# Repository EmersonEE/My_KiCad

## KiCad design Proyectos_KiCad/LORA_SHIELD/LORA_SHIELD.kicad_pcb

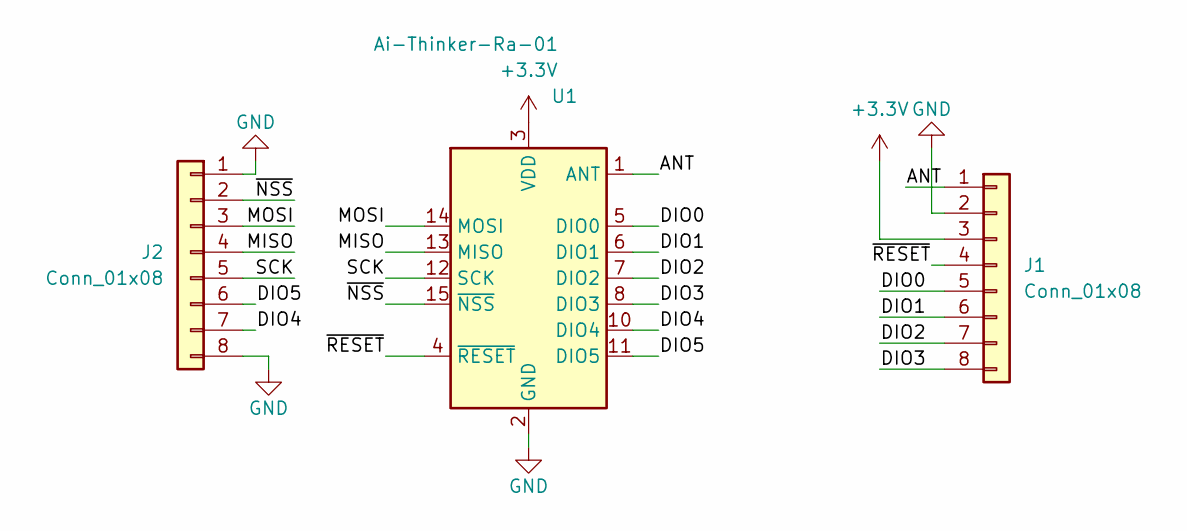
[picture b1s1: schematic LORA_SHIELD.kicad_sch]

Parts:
J1, J2: Conn_01x08; PinHeader_1x08_P2.54mm_Vertical
U1: Ai-Thinker-Ra-01; Ai-Thinker-Ra-01-LoRa

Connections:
+3.3V: J1.3, U1.3 (VDD)
/ANT: J1.1, U1.1 (ANT)
/DIO0: J1.5, U1.5 (DIO0)
/DIO1: J1.6, U1.6 (DIO1)
/DIO2: J1.7, U1.7 (DIO2)
/DIO3: J1.8, U1.8 (DIO3)
/DIO4: J2.7, U1.10 (DIO4)
/DIO5: J2.6, U1.11 (DIO5)
/MISO: J2.4, U1.13 (MISO)
/MOSI: J2.3, U1.14 (MOSI)
/SCK: J2.5, U1.12 (SCK)
/~NSS: J2.2, U1.15 (~NSS)
/~RESET: J1.4, U1.4 (~RESET)
GND: J1.2, J2.1, J2.8, U1.2 (GND), U1.9 (GND), U1.16 (GND)

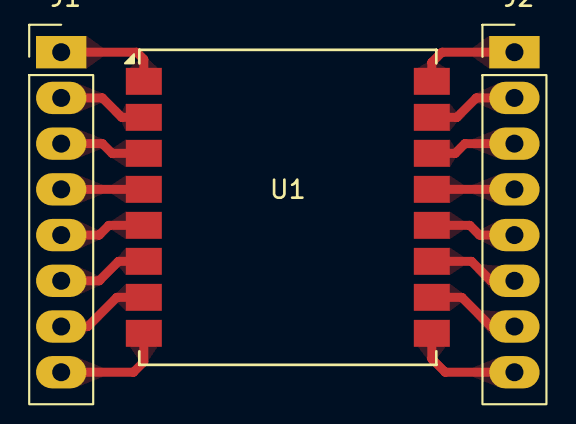
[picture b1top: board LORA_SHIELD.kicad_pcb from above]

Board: 2 copper layers, 3 parts (0 on the bottom side), 14 nets.

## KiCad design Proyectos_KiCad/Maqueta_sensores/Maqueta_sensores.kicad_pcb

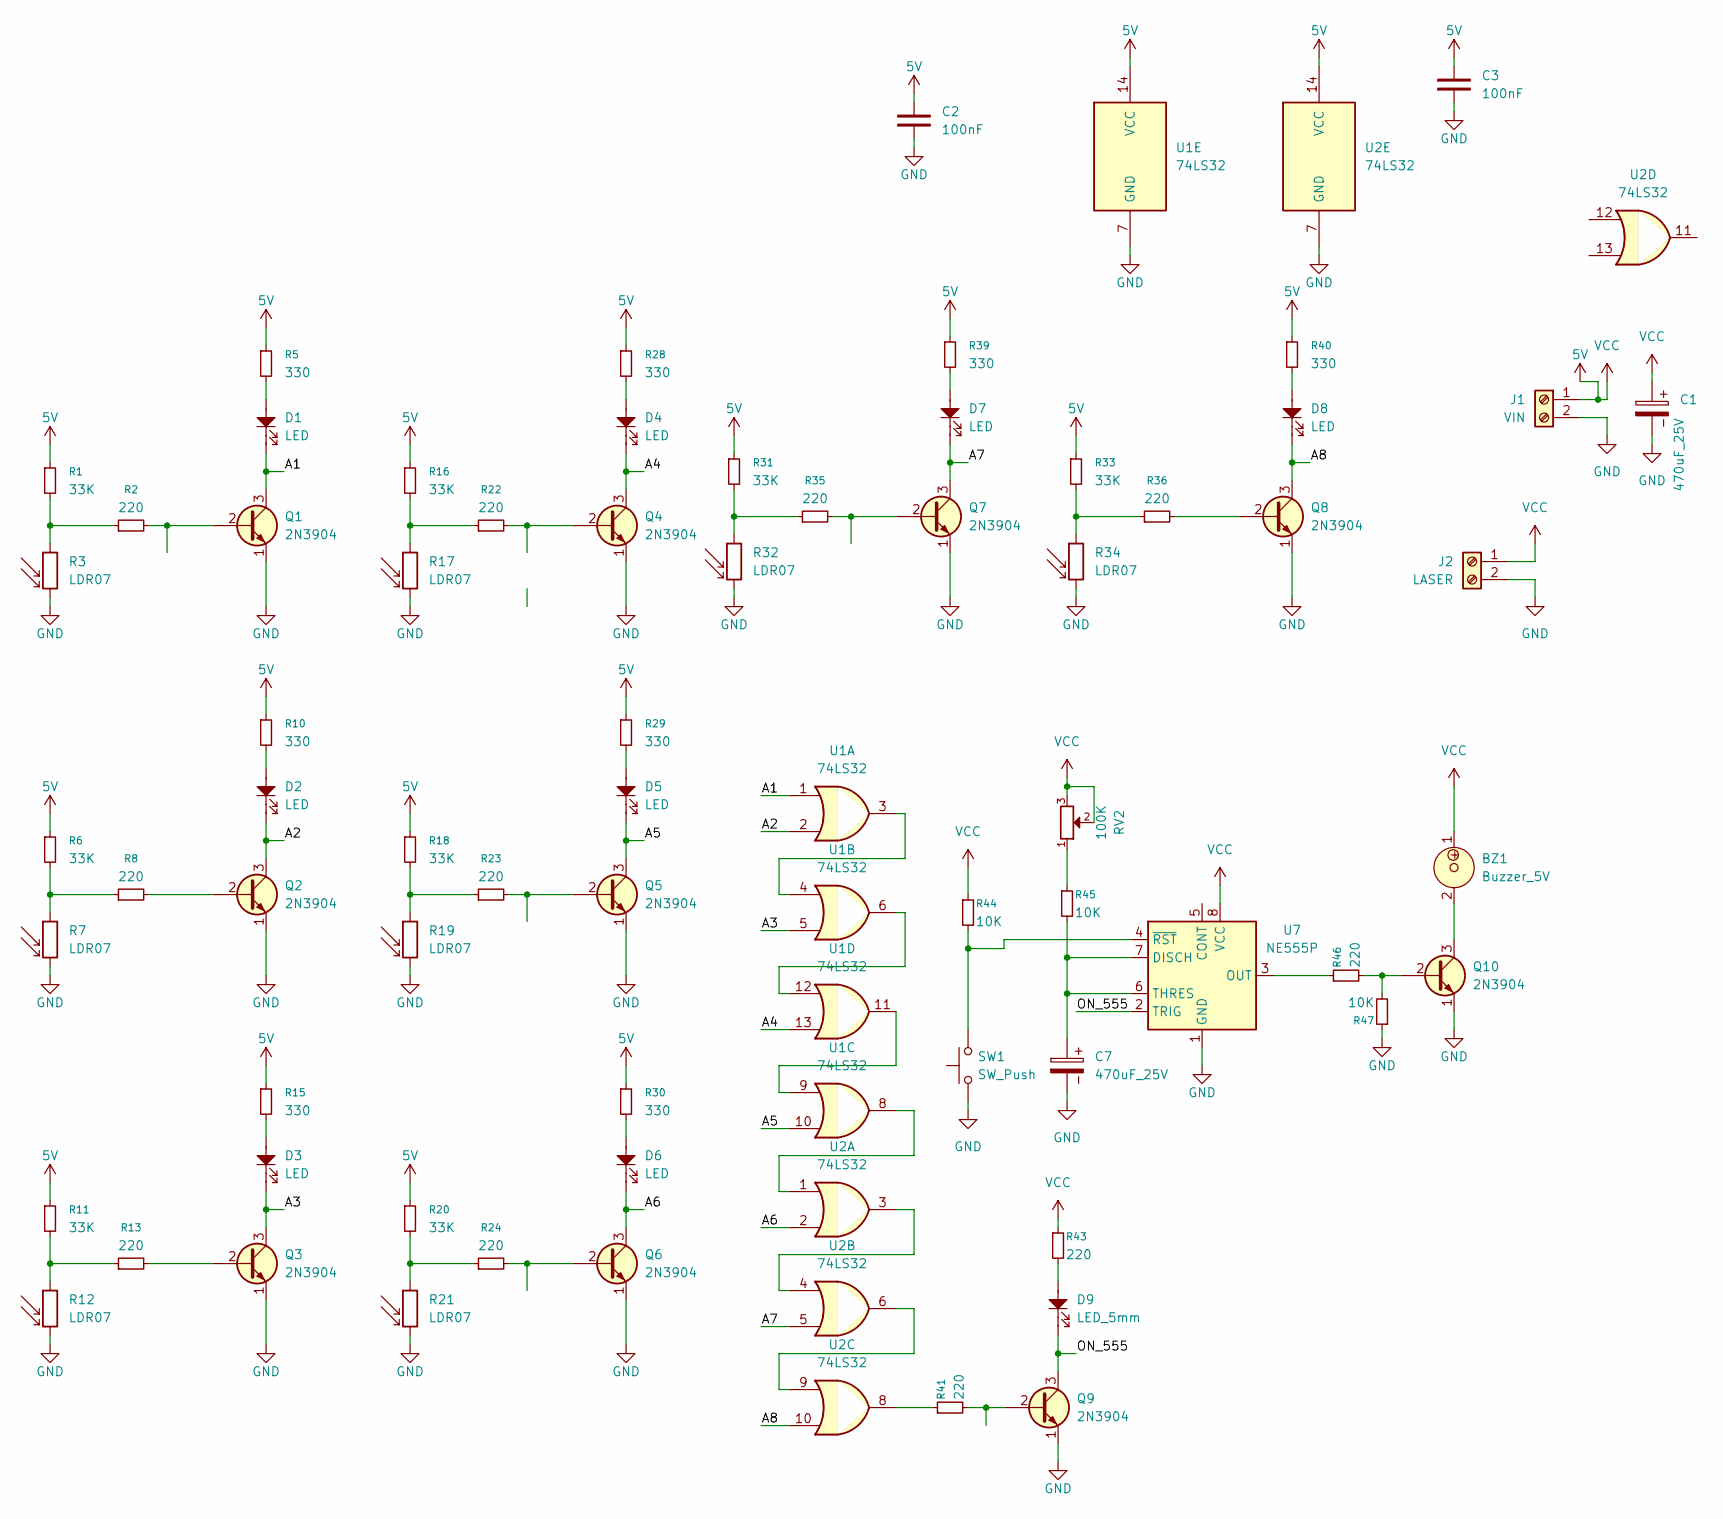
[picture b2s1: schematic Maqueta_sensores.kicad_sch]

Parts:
BZ1: Buzzer_5V; MagneticBuzzer_ProSignal_ABT-410-RC
C1, C7: 470uF_25V; CP_Radial_D8.0mm_P3.50mm
C2, C3: 100nF; C_Disc_D5.0mm_W2.5mm_P2.50mm
D1, D2, D3, D4, D5, D6, D7, D8: LED; LED_D5.0mm
D9: LED_5mm; LED_D5.0mm_Clear
J1: VIN; TerminalBlock_Phoenix_MKDS-1,5-2-5.08_1x02_P5.08mm_Horizont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
J2: LASER; TerminalBlock_Phoenix_MKDS-1,5-2-5.08_1x02_P5.08mm_Horizont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
Q1, Q2, Q3, Q4, Q5, Q6, Q7, Q8, Q9, Q10: 2N3904; TO-92_Inline_Wide_EBC
R1, R6, R11, R16, R18, R20, R31, R33: 33K; R_Axial_DIN0207_L6.3mm_D2.5mm_P10.16mm_Horizontal
R2, R8, R13, R22, R23, R24, R35, R36, R41, R43, R46: 220; R_Axial_DIN0207_L6.3mm_D2.5mm_P10.16mm_Horizontal
R3, R7, R12, R17, R19, R21, R32, R34: LDR07; R_LDR_5.1x4.3mm_P3.4mm_Vertical
R5, R10, R15, R28, R29, R30, R39, R40: 330; R_Axial_DIN0207_L6.3mm_D2.5mm_P10.16mm_Horizontal
R44, R45, R47: 10K; R_Axial_DIN0207_L6.3mm_D2.5mm_P10.16mm_Horizontal
RV2: 100K; Potentiometer_Alps_RK163_Single_Horizontal
SW1: SW_Push; SW_PUSH_6mm
U1, U2: 74LS32; DIP-14_W7.62mm_LongPads
U7: NE555P; DIP-8_W7.62mm_LongPads

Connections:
5V: BZ1.1, C1.1, C2.2, C3.2, J1.1, J2.1, R1.1, R5.1, R6.1, R10.1, R11.1, R15.1, R16.1, R18.1, R20.1, R28.1, R29.1, R30.1, R31.1, R33.1, R39.1, R40.1, R43.1, R44.1, RV2.2, RV2.3, U1.14 (VCC), U2.14 (VCC), U7.8 (VCC)
/A1: D1.1, Q1.3 (C), U1.1
/A2: D2.1, Q2.3 (C), U1.2
/A3: D3.1, Q3.3 (C), U1.5
/A4: D4.1, Q4.3 (C), U1.13
/A5: D5.1, Q5.3 (C), U1.10
/A6: D6.1, Q6.3 (C), U2.2
/A7: D7.1, Q7.3 (C), U2.5
/A8: D8.1, Q8.3 (C), U2.10
/ON_555: D9.1, Q9.3 (C), U7.2 (TRIG)
GND: C1.2, C2.1, C3.1, C7.2, J1.2, J2.2, Q1.1 (E), Q2.1 (E), Q3.1 (E), Q4.1 (E), Q5.1 (E), Q6.1 (E), Q7.1 (E), Q8.1 (E), Q9.1 (E), Q10.1 (E), R3.2, R7.2, R12.2, R17.2, R19.2, R21.2, R32.2, R34.2, R47.1, SW1.1, U1.7 (GND), U2.7 (GND), U7.1 (GND); also elsewhere on the board
unnamed: D1.2, R5.2
unnamed: D2.2, R10.2
unnamed: D3.2, R15.2
unnamed: D4.2, R28.2
unnamed: D5.2, R29.2
unnamed: D6.2, R30.2
unnamed: D7.2, R39.2
unnamed: D8.2, R40.2
unnamed: D9.2, R43.2
unnamed 20: Q1.2 (B), R2.2; also elsewhere on the board
unnamed 21: Q2.2 (B), R8.2; also elsewhere on the board
unnamed 22: Q3.2 (B), R13.2; also elsewhere on the board
unnamed 23: Q4.2 (B), R22.2; also elsewhere on the board
unnamed 24: Q5.2 (B), R23.2; also elsewhere on the board
unnamed 25: Q6.2 (B), R24.2; also elsewhere on the board
unnamed 26: Q7.2 (B), R35.2; also elsewhere on the board
unnamed 27: Q8.2 (B), R36.2; also elsewhere on the board
unnamed 28: Q9.2 (B), R41.2; also elsewhere on the board
unnamed: Q10.2 (B), R46.2, R47.2
unnamed: BZ1.2, Q10.3 (C)
unnamed: R1.2, R2.1, R3.1
unnamed: R6.2, R7.1, R8.1
unnamed: R11.2, R12.1, R13.1
unnamed: R16.2, R17.1, R22.1
unnamed: R18.2, R19.1, R23.1
unnamed: R20.2, R21.1, R24.1
unnamed: R31.2, R32.1, R35.1
unnamed: R33.2, R34.1, R36.1
unnamed: R41.1, U2.8
unnamed: R45.1, RV2.1
unnamed: U1.3, U1.4
unnamed: U1.8, U2.1
unnamed: U1.9, U1.11
unnamed: U1.6, U1.12
unnamed: U2.3, U2.4
unnamed: U2.6, U2.9
unnamed: C7.1, R45.2, U7.6 (THRES), U7.7 (DISCH)
unnamed: R46.1, U7.3 (OUT)
unnamed: R44.2, SW1.2, U7.4 (~RST)

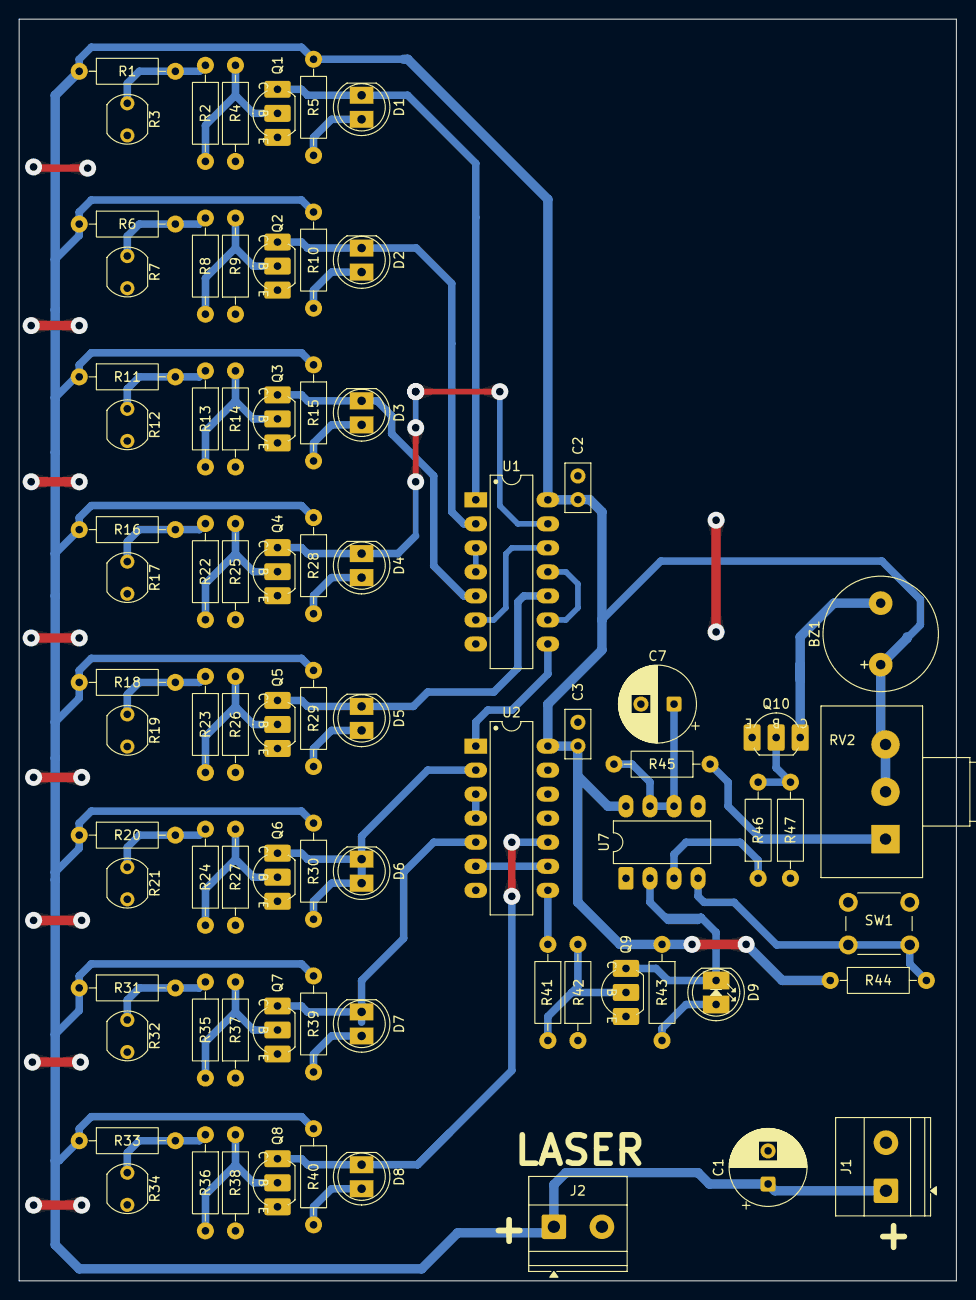
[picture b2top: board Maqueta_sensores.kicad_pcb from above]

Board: 2 copper layers, 99.1 x 133.4 mm, 78 parts (0 on the bottom side), 50 nets.

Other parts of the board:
R4, R9, R14, R25, R26, R27, R37, R38, R42: 10K; R_Axial_DIN0207_L6.3mm_D2.5mm_P10.16mm_Horizontal

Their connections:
GND: R4.1, R9.1, R14.1, R25.1, R26.1, R27.1, R37.1, R38.1, R42.1; also elsewhere on the board
unnamed 20: R4.2; also elsewhere on the board
unnamed 21: R9.2; also elsewhere on the board
unnamed 22: R14.2; also elsewhere on the board
unnamed 23: R25.2; also elsewhere on the board
unnamed 24: R26.2; also elsewhere on the board
unnamed 25: R27.2; also elsewhere on the board
unnamed 26: R37.2; also elsewhere on the board
unnamed 27: R38.2; also elsewhere on the board
unnamed 28: R42.2; also elsewhere on the board

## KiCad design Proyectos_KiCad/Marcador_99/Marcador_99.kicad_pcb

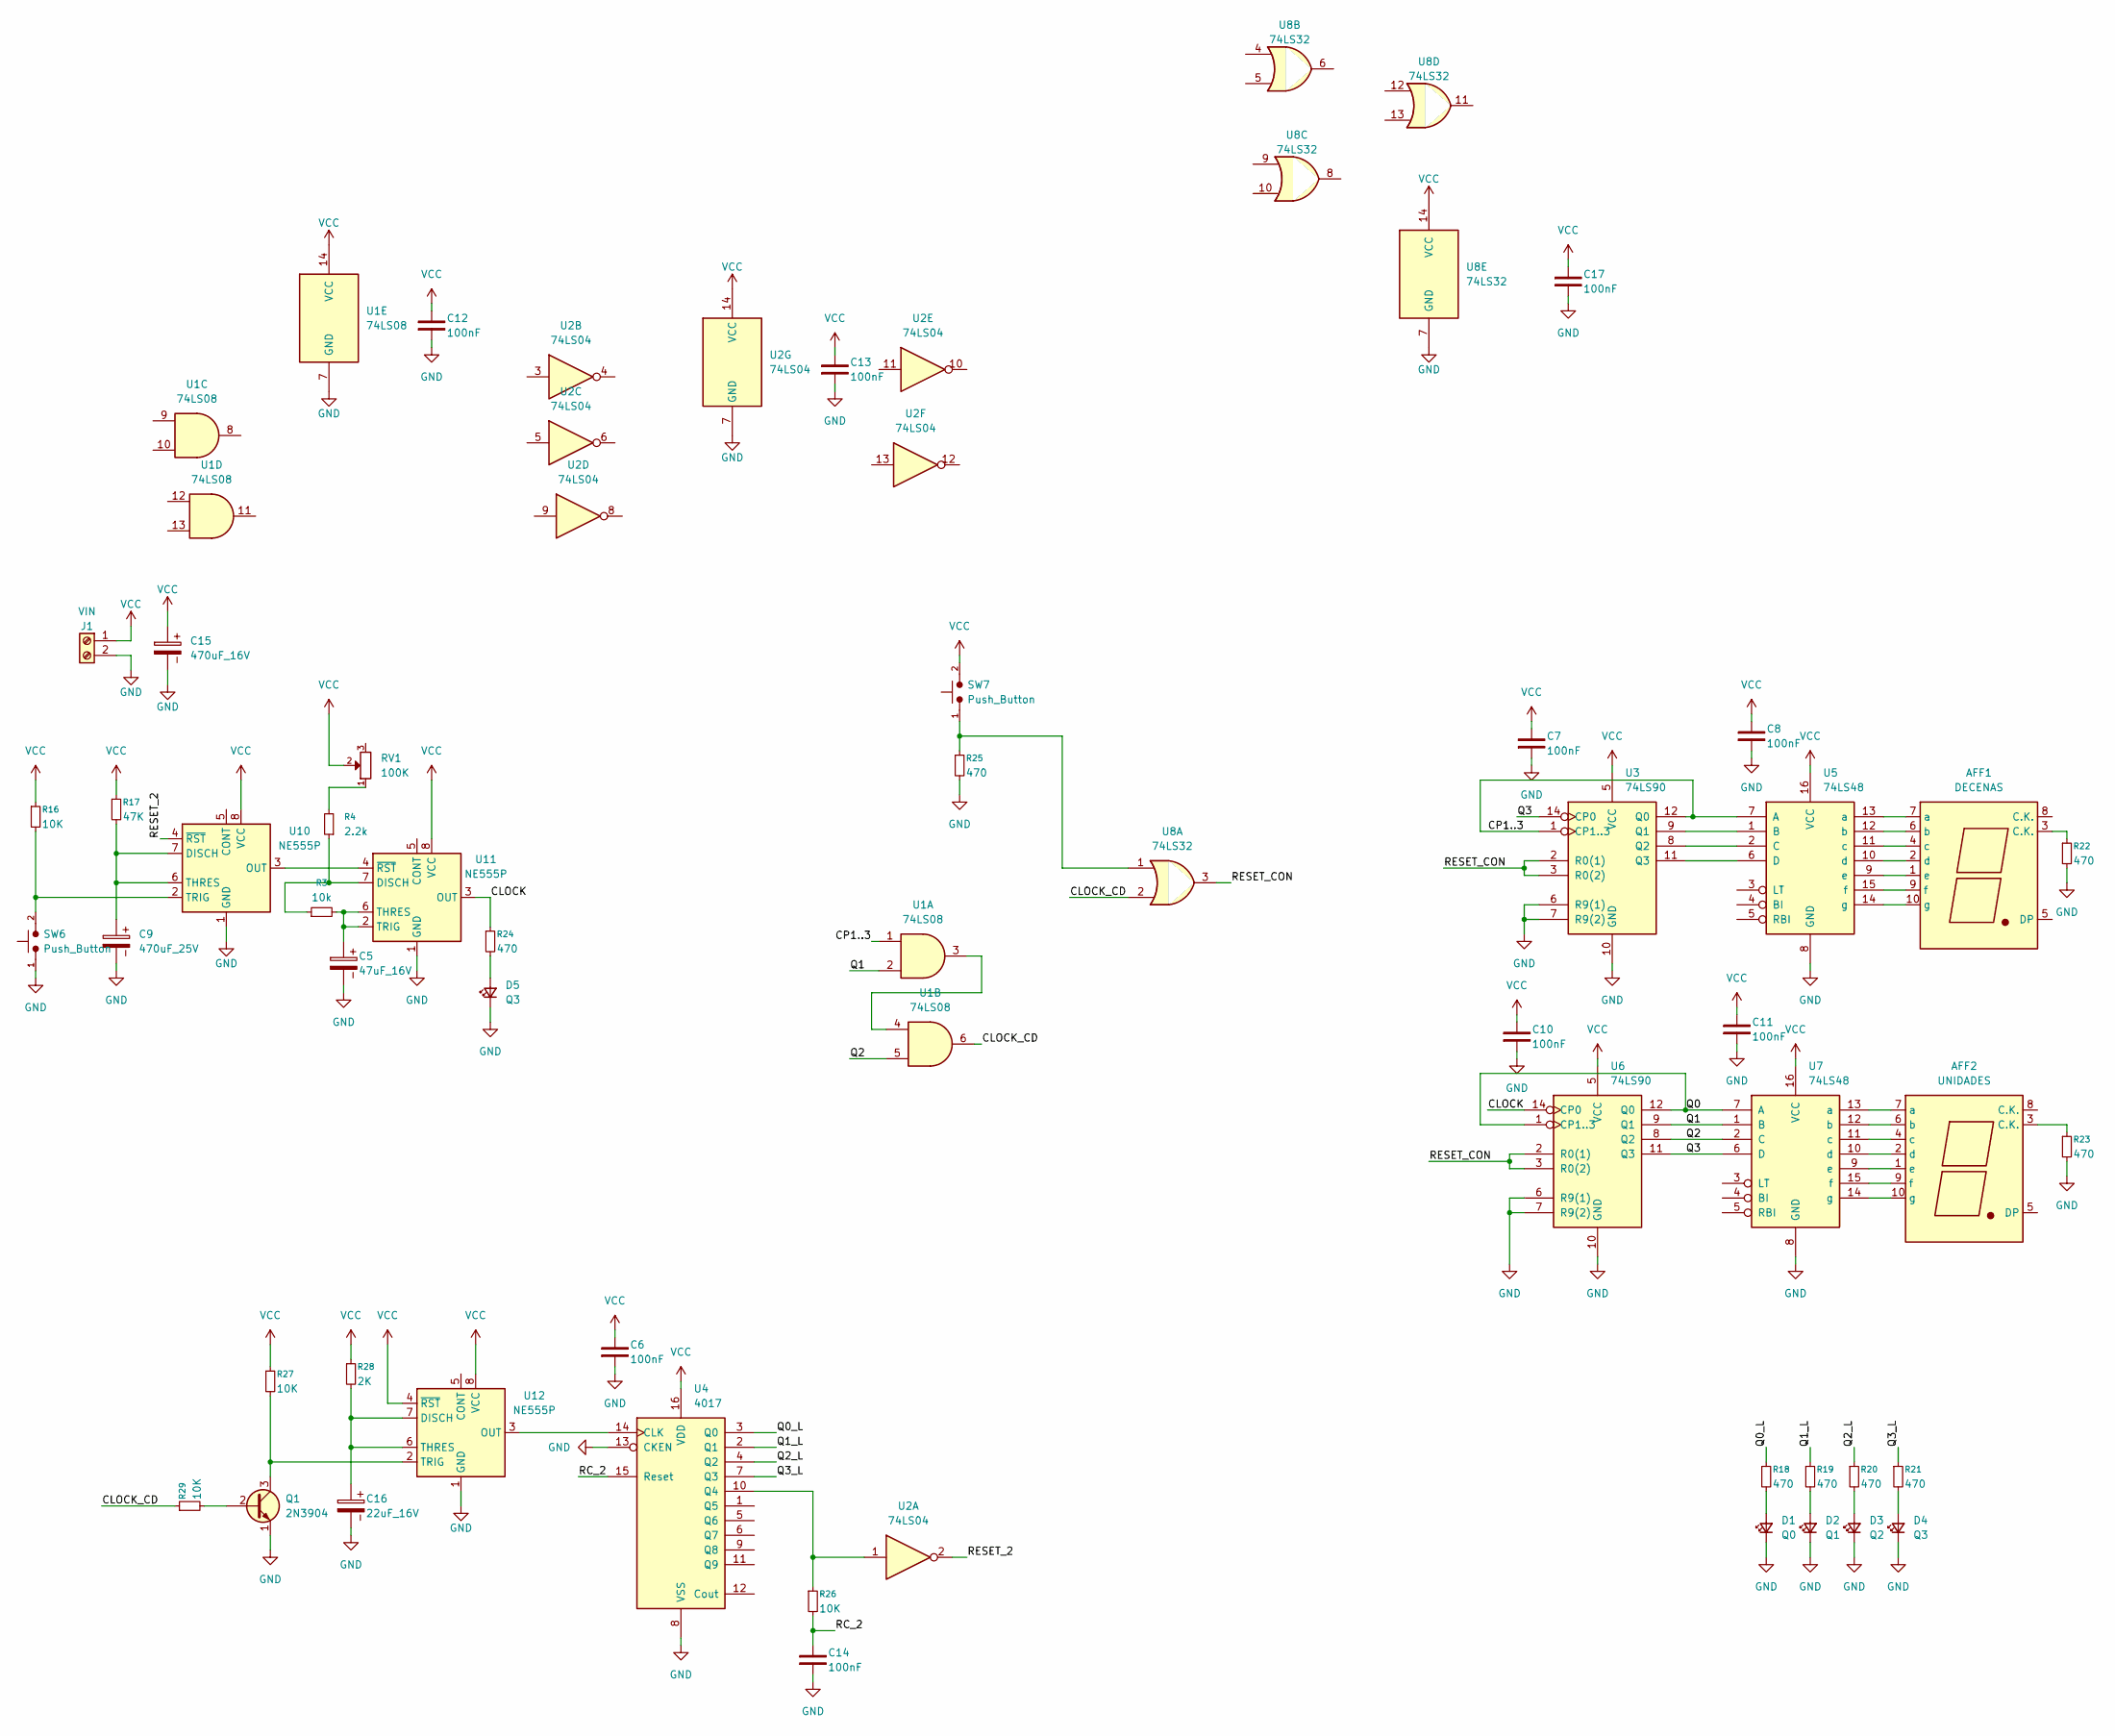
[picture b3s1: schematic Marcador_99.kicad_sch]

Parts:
AFF1: DECENAS; 7SegmentLED_LTS6760_LTS6780
AFF2: UNIDADES; 7SegmentLED_LTS6760_LTS6780
C5: 47uF_16V; CP_Radial_D5.0mm_P2.00mm
C6, C7, C8, C10, C11, C12, C13, C14, C17: 100nF; C_Disc_D5.0mm_W2.5mm_P2.50mm
C9: 470uF_25V; CP_Radial_D8.0mm_P3.50mm
C15: 470uF_16V; CP_Radial_D8.0mm_P3.50mm
C16: 22uF_16V; CP_Radial_D5.0mm_P2.00mm
D1: Q0; LED_D5.0mm
D2: Q1; LED_D5.0mm
D3: Q2; LED_D5.0mm
D4, D5: Q3; LED_D5.0mm
J1: VIN; TerminalBlock_Phoenix_MKDS-1,5-2-5.08_1x02_P5.08mm_Horizont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
Q1: 2N3904; TO-92_Inline_Wide_EBC
R3: 10k; 10K
R4: 2.2k; 10K
R16, R26, R27, R29: 10K
R17: 47K; 10K
R18, R19, R20, R21, R22, R23, R24, R25: 470; 10K
R28: 2K; 10K
RV1: 100K; Potentiometer_RM065
SW6, SW7: Push_Button; SW_PUSH_6mm
U1: 74LS08; DIP-14_W7.62mm_LongPads
U2: 74LS04; DIP-14_W7.62mm_LongPads
U3, U6: 74LS90; DIP-14_W7.62mm_LongPads
U4: 4017; DIP-16_W7.62mm_LongPads
U5, U7: 74LS48; DIP-16_W7.62mm_LongPads
U8: 74LS32; DIP-14_W7.62mm_LongPads
U10, U11, U12: NE555P; DIP-8_W7.62mm_LongPads

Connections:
/CLOCK: R24.1, U6.14 (CP0), U11.3 (OUT)
/CLOCK_CD: R29.1, U1.6, U8.2
/CP1..3: U1.1, U3.1 (CP1..3), U3.12 (Q0), U5.7 (A)
/Q0: U6.1 (CP1..3), U6.12 (Q0), U7.7 (A)
/Q0_L: R18.1, U4.3 (Q0)
/Q1: U1.2, U6.9 (Q1), U7.1 (B)
/Q1_L: R19.1, U4.2 (Q1)
/Q2: U1.5, U6.8 (Q2), U7.2 (C)
/Q2_L: R20.1, U4.4 (Q2)
/Q3: U3.14 (CP0), U6.11 (Q3), U7.6 (D)
/Q3_L: R21.1, U4.7 (Q3)
/RC_2: C14.2, R26.2, U4.15 (Reset)
/RESET_2: U2.2, U10.4 (~RST)
/RESET_CON: U3.2 (R0(1)), U3.3 (R0(2)), U6.2 (R0(1)), U6.3 (R0(2)), U8.3
GND: C5.2, C6.1, C7.1, C8.1, C9.2, C10.1, C11.1, C12.1, C13.1, C14.1, C15.2, C16.2, C17.1, D1.1 (K), D2.1 (K), D3.1 (K), D4.1 (K), D5.1 (K), J1.2, Q1.1 (E), R22.2, R23.2, R25.2, SW6.1, U1.7 (GND), U2.7 (GND), U3.6 (R9(1)), U3.7 (R9(2)), U3.10 (GND), U4.8 (VSS), U4.13 (CKEN), U5.8 (GND), U6.6 (R9(1)), U6.7 (R9(2)), U6.10 (GND), U7.8 (GND), U8.7 (GND), U10.1 (GND), U11.1 (GND), U12.1 (GND)
unnamed: AFF1.3 (C.K.), R22.1
unnamed: AFF1.7 (a), U5.13 (a)
unnamed: AFF1.6 (b), U5.12 (b)
unnamed: AFF1.4 (c), U5.11 (c)
unnamed: AFF1.2 (d), U5.10 (d)
unnamed: AFF1.1 (e), U5.9 (e)
unnamed: AFF1.9 (f), U5.15 (f)
unnamed: AFF1.10 (g), U5.14 (g)
unnamed: AFF2.3 (C.K.), R23.1
unnamed: AFF2.7 (a), U7.13 (a)
unnamed: AFF2.6 (b), U7.12 (b)
unnamed: AFF2.4 (c), U7.11 (c)
unnamed: AFF2.2 (d), U7.10 (d)
unnamed: AFF2.1 (e), U7.9 (e)
unnamed: AFF2.9 (f), U7.15 (f)
unnamed: AFF2.10 (g), U7.14 (g)
unnamed: D1.2 (A), R18.2
unnamed: D2.2 (A), R19.2
unnamed: D3.2 (A), R20.2
unnamed: D4.2 (A), R21.2
unnamed: D5.2 (A), R24.2
unnamed: Q1.2 (B), R29.2
unnamed: Q1.3 (C), R27.2, U12.2 (TRIG)
unnamed: R4.2, RV1.1
unnamed: R25.1, SW7.1, U8.1
unnamed: U1.3, U1.4
unnamed: U3.9 (Q1), U5.1 (B)
unnamed: U3.8 (Q2), U5.2 (C)
unnamed: U3.11 (Q3), U5.6 (D)
unnamed: R26.1, U2.1, U4.10 (Q4)
unnamed: C9.1, R17.2, U10.6 (THRES), U10.7 (DISCH)
unnamed: U10.3 (OUT), U11.4 (~RST)
unnamed: R16.2, SW6.2, U10.2 (TRIG)
unnamed: R3.1, R4.1, U11.7 (DISCH)
unnamed: C5.1, R3.2, U11.2 (TRIG), U11.6 (THRES)
unnamed: C16.1, R28.2, U12.6 (THRES), U12.7 (DISCH)
unnamed: U4.14 (CLK), U12.3 (OUT)
VCC: C6.2, C7.2, C8.2, C10.2, C11.2, C12.2, C13.2, C15.1, C17.2, J1.1, R16.1, R17.1, R27.1, R28.1, RV1.2, SW7.2, U1.14 (VCC), U2.14 (VCC), U3.5 (VCC), U4.16 (VDD), U5.16 (VCC), U6.5 (VCC), U7.16 (VCC), U8.14 (VCC), U10.8 (VCC), U11.8 (VCC), U12.4 (~RST), U12.8 (VCC)

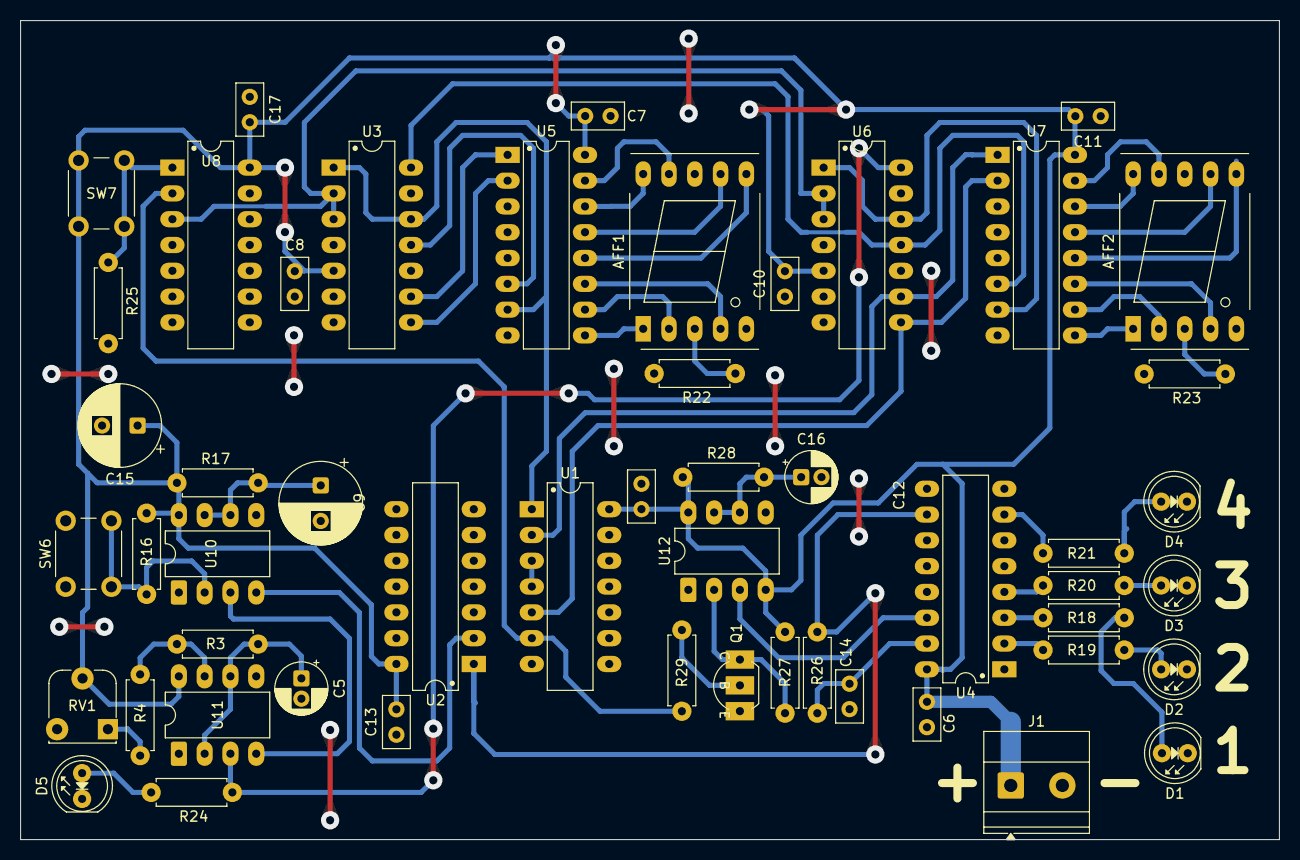
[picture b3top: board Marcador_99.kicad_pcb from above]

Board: 2 copper layers, 124.0 x 80.6 mm, 52 parts (0 on the bottom side), 53 nets.

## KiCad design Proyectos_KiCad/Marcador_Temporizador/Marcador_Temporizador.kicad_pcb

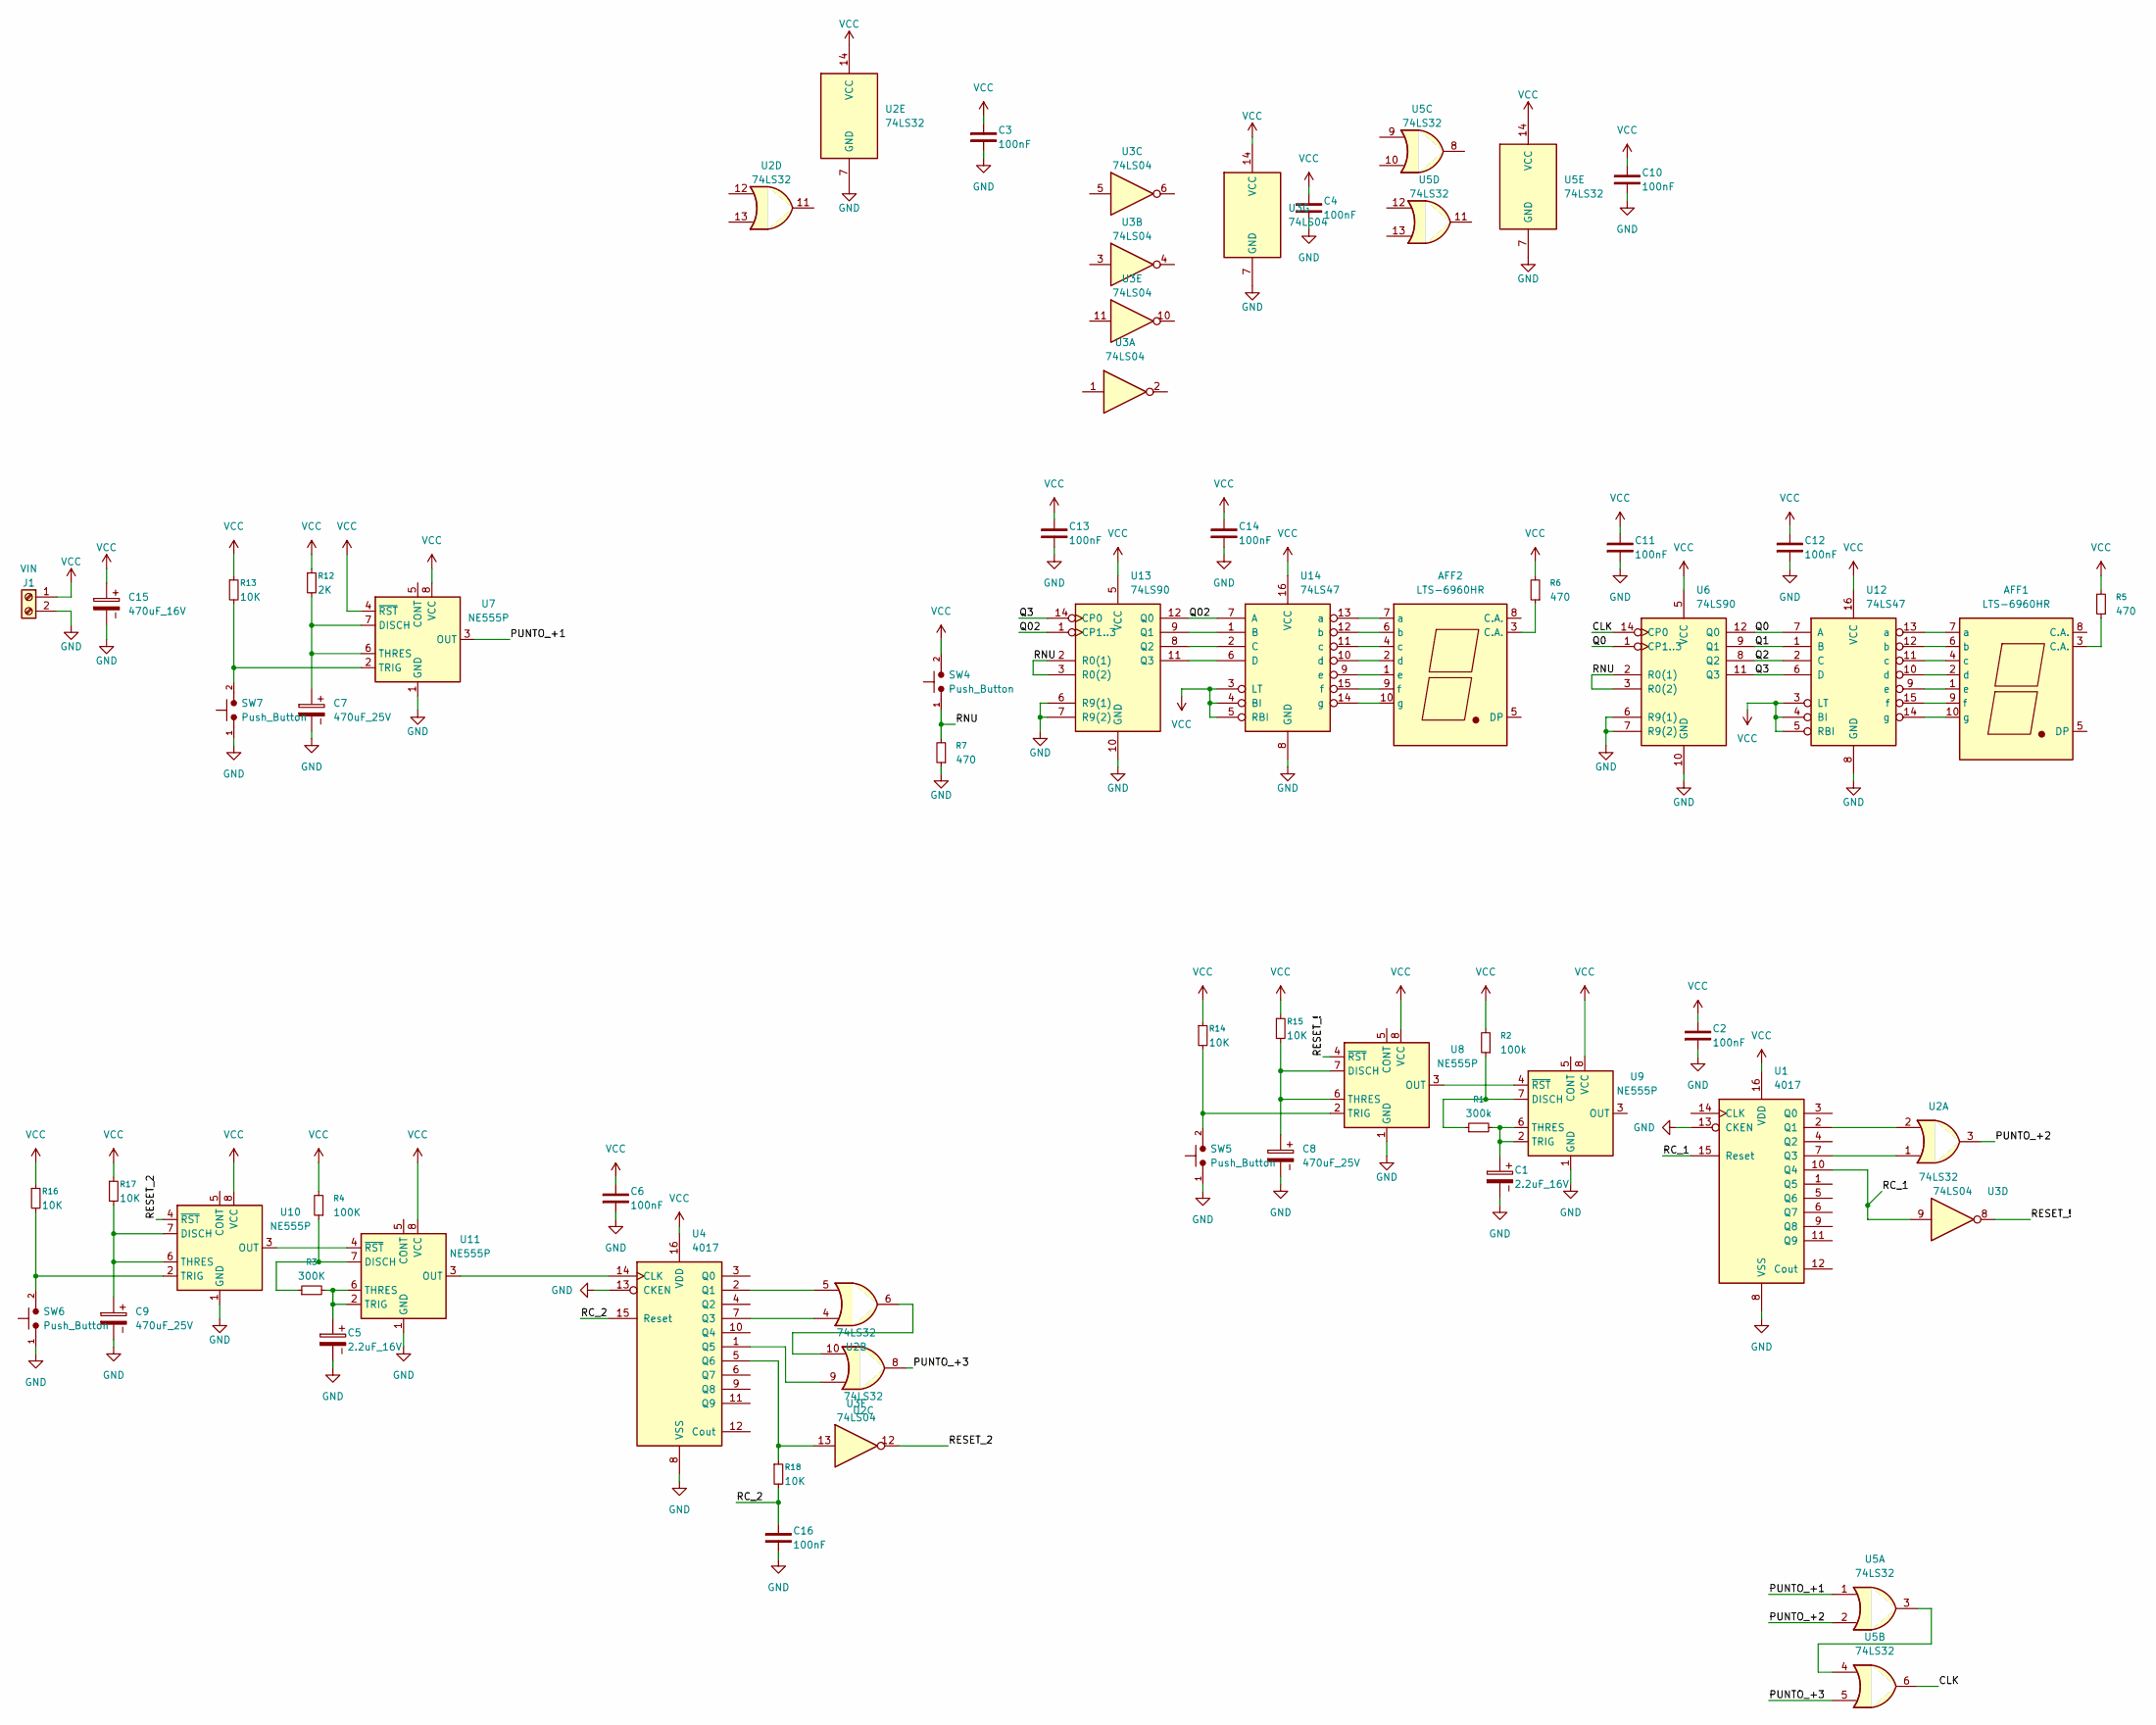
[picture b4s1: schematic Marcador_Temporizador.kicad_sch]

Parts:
AFF1, AFF2: LTS-6960HR; 7SegmentLED_LTS6760_LTS6780
C1, C5: 2.2uF_16V; CP_Radial_D5.0mm_P2.00mm
C2, C3, C4, C6, C10, C11, C12, C13, C14, C16: 100nF; C_Disc_D5.0mm_W2.5mm_P2.50mm
C7, C8, C9: 470uF_25V; CP_Radial_D8.0mm_P3.50mm
C15: 470uF_16V; CP_Radial_D8.0mm_P3.50mm
J1: VIN; TerminalBlock_Phoenix_MKDS-1,5-2-5.08_1x02_P5.08mm_Horizont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
R1: 300k; 10K
R2: 100k; 10K
R3: 300K; 10K
R4: 100K; 10K
R5, R6, R7: 470
R12: 2K; 10K
R13, R14, R15, R16, R17, R18: 10K
SW4, SW5, SW6, SW7: Push_Button; SW_PUSH_6mm
U1, U4: 4017; DIP-16_W7.62mm_LongPads
U2, U5: 74LS32; DIP-14_W7.62mm_LongPads
U3: 74LS04; DIP-14_W7.62mm_LongPads
U6, U13: 74LS90; DIP-14_W7.62mm_LongPads
U7, U8, U9, U10, U11: NE555P; DIP-8_W7.62mm_LongPads
U12, U14: 74LS47; DIP-16_W7.62mm_LongPads

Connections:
/CLK: U5.6, U6.14 (CP0)
/PUNTO_+1: U5.1, U7.3 (OUT)
/PUNTO_+2: U2.3, U5.2
/PUNTO_+3: U2.8, U5.5
/Q0: U6.1 (CP1..3), U6.12 (Q0), U12.7 (A)
/Q1: U6.9 (Q1), U12.1 (B)
/Q02: U13.1 (CP1..3), U13.12 (Q0), U14.7 (A)
/Q2: U6.8 (Q2), U12.2 (C)
/Q3: U6.11 (Q3), U12.6 (D), U13.14 (CP0)
/RC_1: U1.10 (Q4), U1.15 (Reset), U3.9
/RESET_2: U3.12, U10.4 (~RST)
/RESET_!: U3.8, U8.4 (~RST)
/RNU: R7.2, SW4.1, U6.2 (R0(1)), U6.3 (R0(2)), U13.2 (R0(1)), U13.3 (R0(2))
GND: C1.2, C2.1, C3.1, C4.1, C5.2, C6.1, C7.2, C8.2, C9.2, C10.1, C11.1, C12.1, C13.1, C14.1, C15.2, C16.1, J1.2, R7.1, SW5.1, SW6.1, SW7.1, U1.8 (VSS), U1.13 (CKEN), U2.7 (GND), U3.7 (GND), U4.8 (VSS), U4.13 (CKEN), U5.7 (GND), U6.6 (R9(1)), U6.7 (R9(2)), U6.10 (GND), U7.1 (GND), U8.1 (GND), U9.1 (GND), U10.1 (GND), U11.1 (GND), U12.8 (GND), U13.6 (R9(1)), U13.7 (R9(2)), U13.10 (GND), U14.8 (GND)
unnamed: AFF1.3 (C.A.), R5.1
unnamed: AFF1.7 (a), U12.13 (a)
unnamed: AFF1.6 (b), U12.12 (b)
unnamed: AFF1.4 (c), U12.11 (c)
unnamed: AFF1.2 (d), U12.10 (d)
unnamed: AFF1.1 (e), U12.9 (e)
unnamed: AFF1.9 (f), U12.15 (f)
unnamed: AFF1.10 (g), U12.14 (g)
unnamed: AFF2.3 (C.A.), R6.1
unnamed: AFF2.7 (a), U14.13 (a)
unnamed: AFF2.6 (b), U14.12 (b)
unnamed: AFF2.4 (c), U14.11 (c)
unnamed: AFF2.2 (d), U14.10 (d)
unnamed: AFF2.1 (e), U14.9 (e)
unnamed: AFF2.9 (f), U14.15 (f)
unnamed: AFF2.10 (g), U14.14 (g)
unnamed: U1.14 (CLK), U9.3 (OUT)
unnamed: U1.2 (Q1), U2.2
unnamed: U1.7 (Q3), U2.1
unnamed: U2.6, U2.10
unnamed: U2.5, U4.2 (Q1)
unnamed: U2.4, U4.7 (Q3)
unnamed: U2.9, U4.1 (Q5)
unnamed: U5.3, U5.4
unnamed: C7.1, R12.2, U7.6 (THRES), U7.7 (DISCH)
unnamed: R13.2, SW7.2, U7.2 (TRIG)
unnamed: C8.1, R15.2, U8.6 (THRES), U8.7 (DISCH)
unnamed: U8.3 (OUT), U9.4 (~RST)
unnamed: R14.2, SW5.2, U8.2 (TRIG)
unnamed: R1.1, R2.1, U9.7 (DISCH)
unnamed: C1.1, R1.2, U9.2 (TRIG), U9.6 (THRES)
unnamed: C9.1, R17.2, U10.6 (THRES), U10.7 (DISCH)
unnamed: U10.3 (OUT), U11.4 (~RST)
unnamed: R16.2, SW6.2, U10.2 (TRIG)
unnamed: R3.1, R4.1, U11.7 (DISCH)
unnamed: U4.14 (CLK), U11.3 (OUT)
unnamed: C5.1, R3.2, U11.2 (TRIG), U11.6 (THRES)
unnamed: U13.9 (Q1), U14.1 (B)
unnamed: U13.8 (Q2), U14.2 (C)
unnamed: U13.11 (Q3), U14.6 (D)
VCC: C2.2, C3.2, C4.2, C6.2, C10.2, C11.2, C12.2, C13.2, C14.2, C15.1, J1.1, R2.2, R4.2, R5.2, R6.2, R12.1, R13.1, R14.1, R15.1, R16.1, R17.1, SW4.2, U1.16 (VDD), U2.14 (VCC), U3.14 (VCC), U4.16 (VDD), U5.14 (VCC), U6.5 (VCC), U7.4 (~RST), U7.8 (VCC), U8.8 (VCC), U9.8 (VCC), U10.8 (VCC), U11.8 (VCC), U12.3 (LT), U12.4 (BI), U12.5 (RBI), U12.16 (VCC), U13.5 (VCC), U14.3 (LT), U14.4 (BI), U14.5 (RBI), U14.16 (VCC)

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
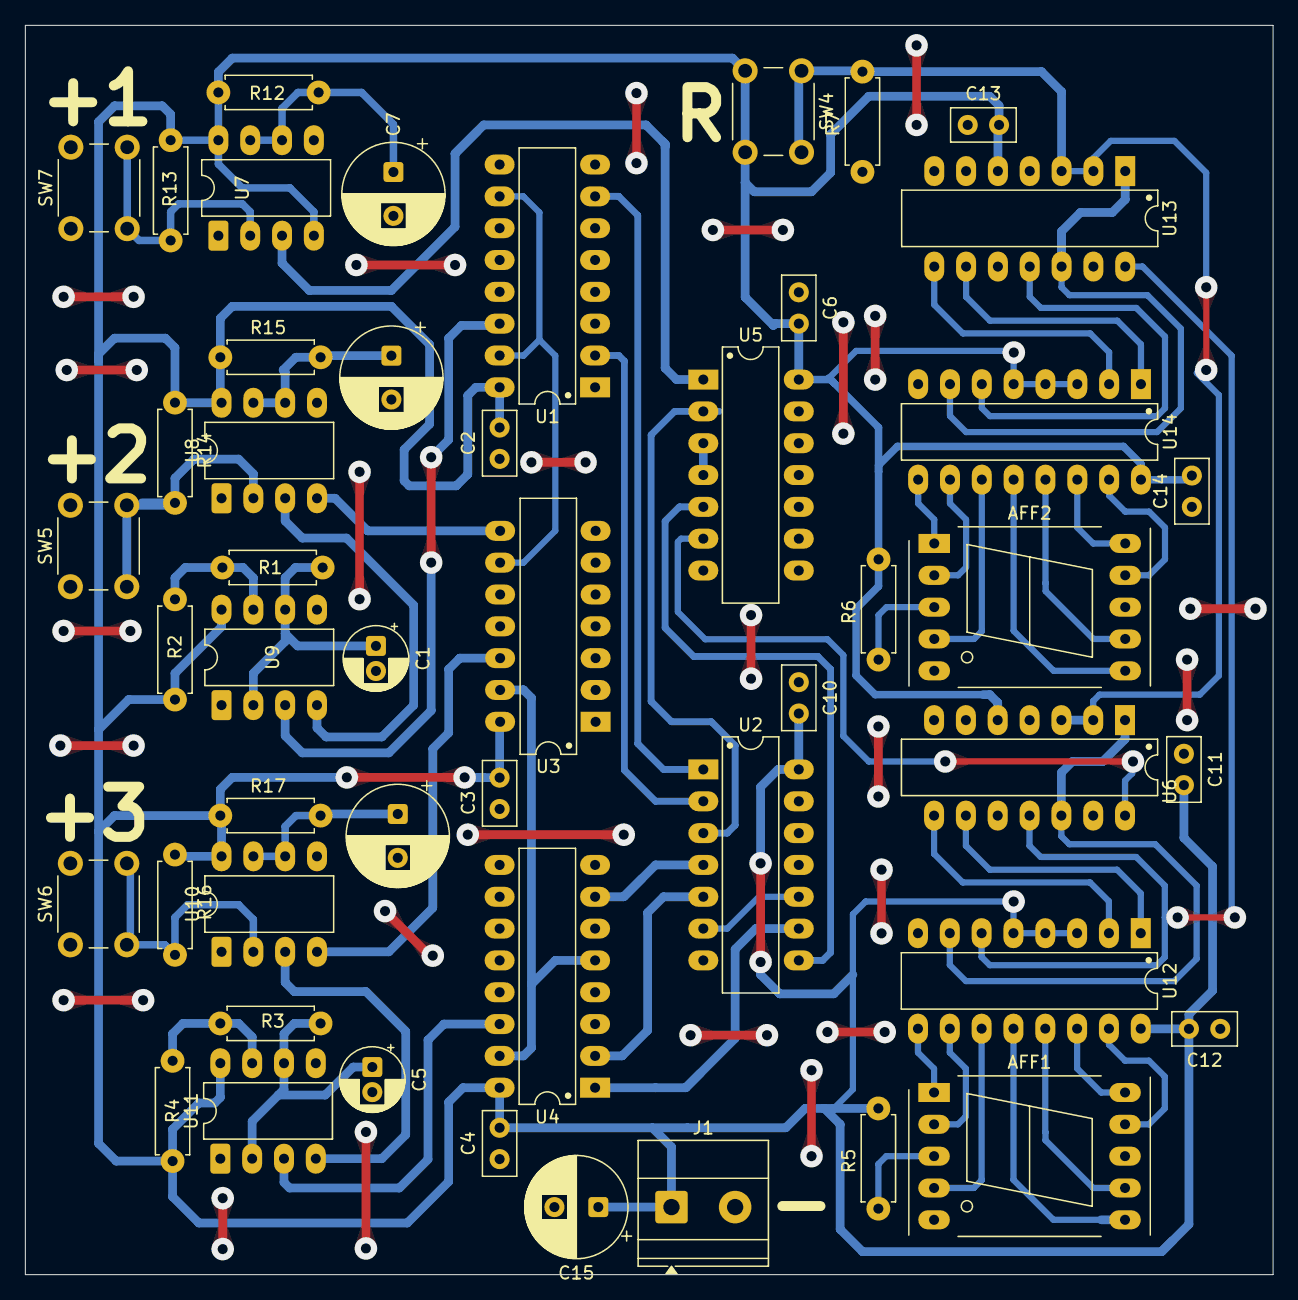
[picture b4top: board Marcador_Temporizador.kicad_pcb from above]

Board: 2 copper layers, 99.6 x 99.7 mm, 49 parts (0 on the bottom side), 56 nets.
